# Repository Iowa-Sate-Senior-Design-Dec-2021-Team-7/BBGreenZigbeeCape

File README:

--Senior Design--
_________________________________________________________________________________________

Title: BeagleBone Green Gateway IoT Hub

Website: https://sddec21-07.sd.ece.iastate.edu

Project email: sddec21-07@iastate.edu

Trello board: https://trello.com/b/s8RNrqa7

Devs:
	-- Parker Larsen (pjlarsen)
	-- Taylor Weil (tcweil)
	-- Sterling Hulling (shulling)
	-- Sean Griffen (griffens)
_________________________________________________________________________________________

See CHANGELOG for official release updates/changes
_________________________________________________________________________________________

Scope:
	-- 
	
Stretch scope:
	-- 
_________________________________________________________________________________________

Requirements (in no particular order):
	-- 
	
Stretch Requirements (in no particular order):
	-- 
_________________________________________________________________________________________

Directory Roles:
	-- hardware: for pcb designs created and other hardware-specific resources
	-- firmware: for code being deployed on the BeagleBone Green Gateway, IoT cape, or other created daughter boards
	-- software: for code not being deployed on a hardware module. i.e. web-servers, apps, and other non-controller code
	-- docs: for project documents and classwork
_________________________________________________________________________________________

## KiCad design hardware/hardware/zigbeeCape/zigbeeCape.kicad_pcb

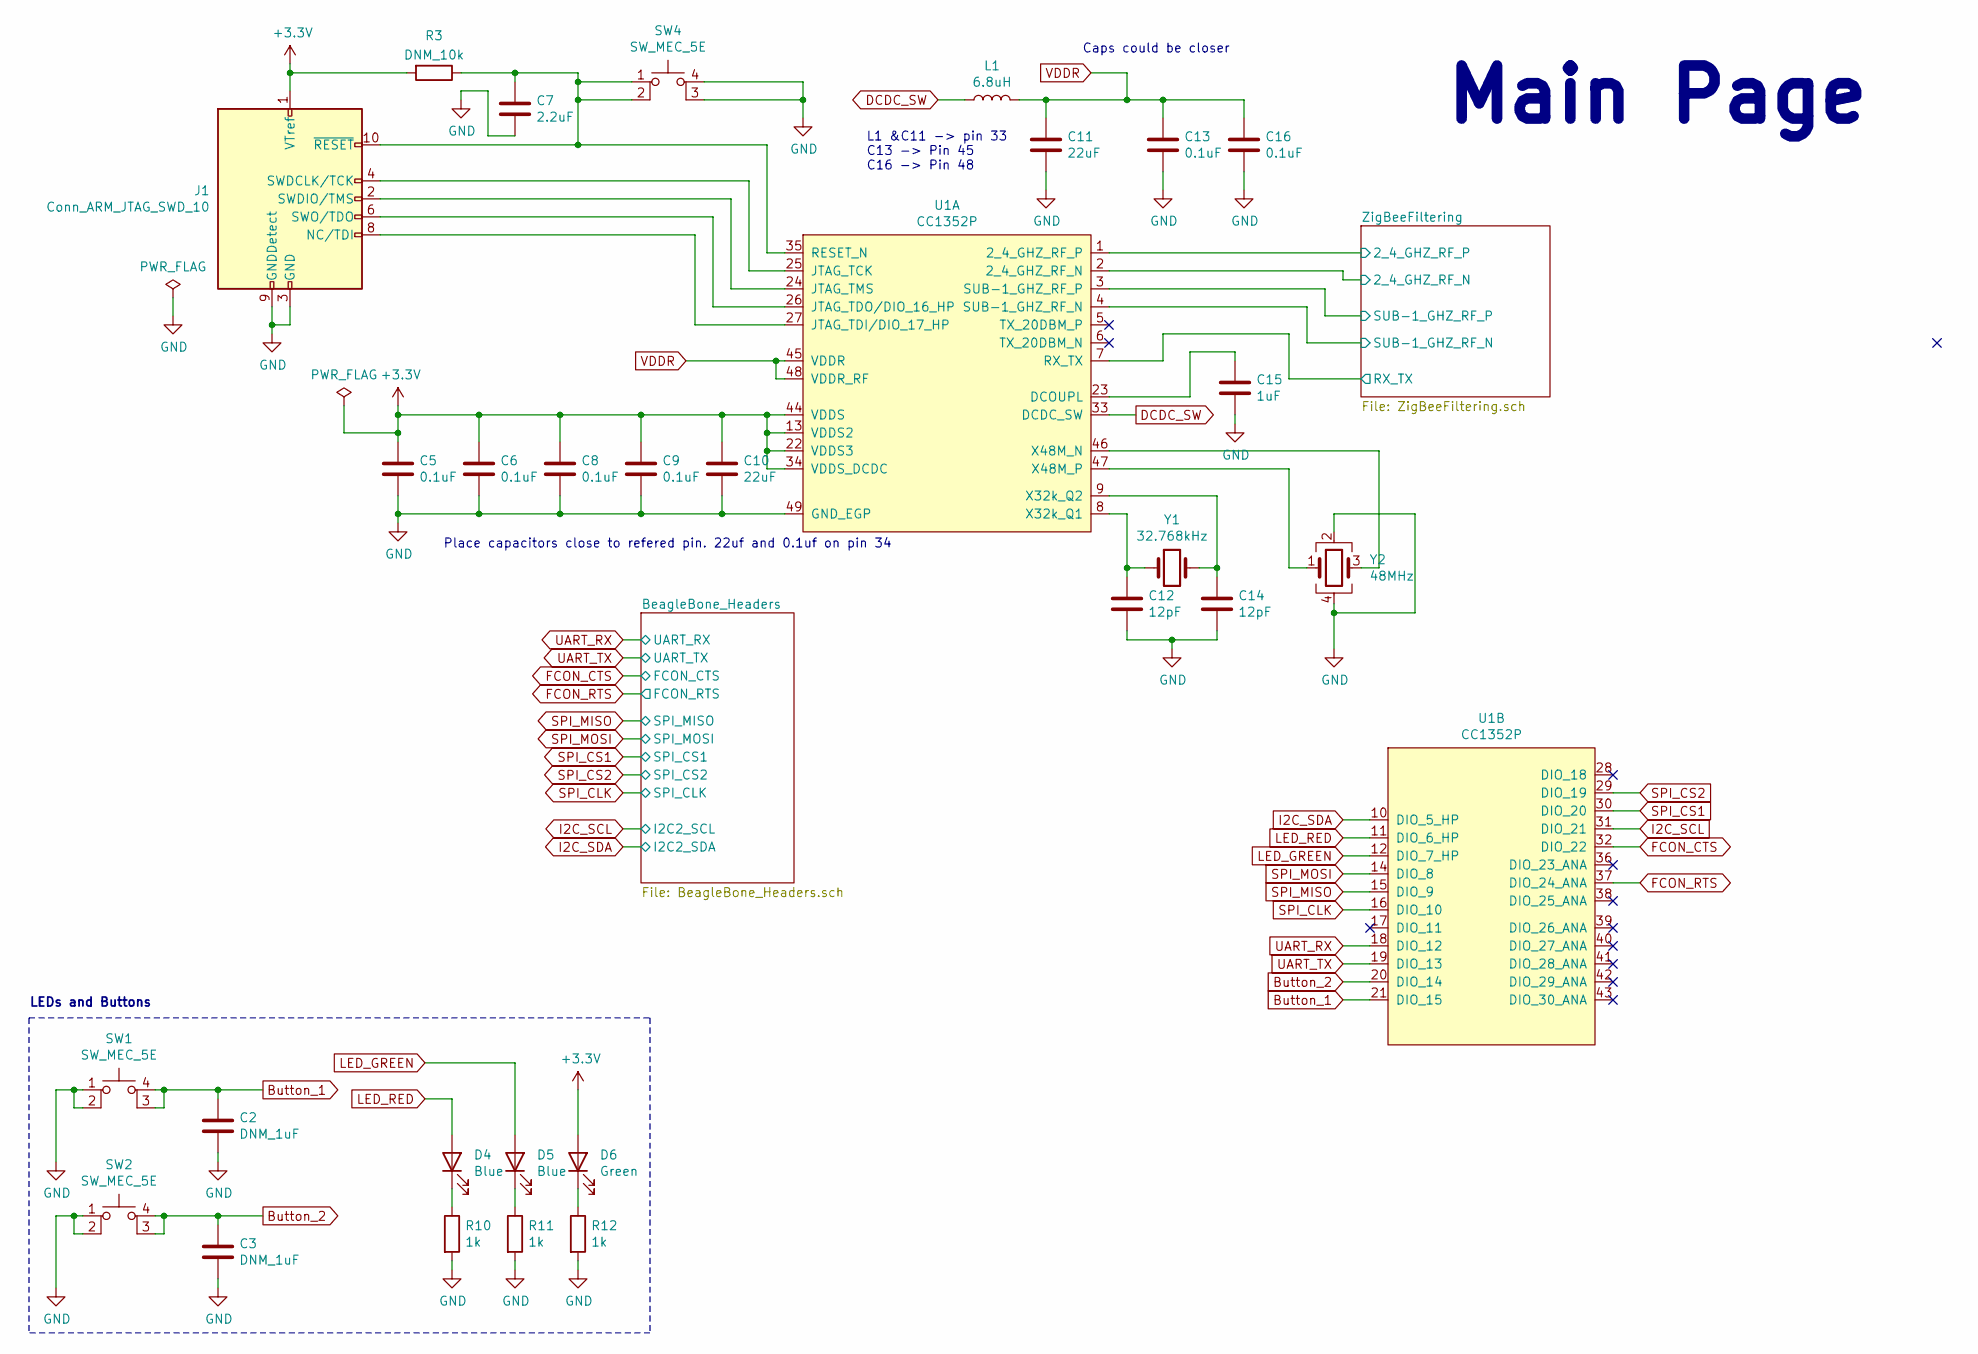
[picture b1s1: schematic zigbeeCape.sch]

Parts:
C2, C3: DNM_1uF; C_0603_1608Metric_Pad1.08x0.95mm_HandSolder; Digikey Part Number 1276-1184-1-ND
C5, C6, C8, C9, C13, C16: 0.1uF; C_0603_1608Metric_Pad1.08x0.95mm_HandSolder; Digikey Part Number 311-1777-1-ND
C7: 2.2uF; C_0603_1608Metric_Pad1.08x0.95mm_HandSolder; Digikey Part Number 1276-1085-1-ND
C10, C11: 22uF; C_0603_1608Metric_Pad1.08x0.95mm_HandSolder; Digikey Part Number 490-7611-1-ND
C12, C14: 12pF; C_0402_1005Metric_Pad0.74x0.62mm_HandSolder; Digikey Part Number 490-5924-1-ND
C15: 1uF; C_0603_1608Metric_Pad1.08x0.95mm_HandSolder; Digikey Part Number 1276-1184-1-ND
D4, D5: Blue; LED_0603_1608Metric_Pad1.05x0.95mm_HandSolder; Digikey Part Number 475-2815-1-ND
D6: Green; LED_0603_1608Metric_Pad1.05x0.95mm_HandSolder; Digikey Part Number 67-2320-1-ND
J1: Conn_ARM_JTAG_SWD_10; Digikey Part Number 1175-1621-ND
L1: 6.8uH; L_0805_2012Metric_Pad1.15x1.40mm_HandSolder; Digikey Part Number 445-17082-1-ND
R3: DNM_10k; R_0603_1608Metric_Pad0.98x0.95mm_HandSolder; Digikey Part Number 13-RT0603FRE1310KLCT-ND
R10, R11, R12: 1k; R_0603_1608Metric_Pad0.98x0.95mm_HandSolder; Digikey Part Number RMCF0603FT1K00CT-ND
SW1, SW2, SW4: SW_MEC_5E; SMD_PUSH_BUTTON; Digikey Part Number 679-2381-1-ND
U1: CC1352P; CC1352R
Y1: 32.768kHz; FC-135_Crystal_Unit; Digikey Part Number 2195-CC5V-T1A-32.768KHZ-7PF-20PPM-TA-QC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
Y2: 48MHz; SXT32418FD16-48MHZ_Crystal; Digikey Part Number 535-13996-1-ND

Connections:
+3V3: C5.1, C6.1, C8.1, C9.1, C10.1, D6.2 (A), J1.1 (VTref), R3.2, U1.13 (VDDS2), U1.22 (VDDS3), U1.34 (VDDS_DCDC), U1.44 (VDDS); also elsewhere on the board
/ZigBeeFiltering/2_4_GHZ_RF_N: U1.2 (2_4_GHZ_RF_N); also elsewhere on the board
/ZigBeeFiltering/2_4_GHZ_RF_P: U1.1 (2_4_GHZ_RF_P); also elsewhere on the board
/ZigBeeFiltering/RX_TX: U1.7 (RX_TX); also elsewhere on the board
/ZigBeeFiltering/SUB-1_GHZ_RF_N: U1.4 (SUB-1_GHZ_RF_N); also elsewhere on the board
/ZigBeeFiltering/SUB-1_GHZ_RF_P: U1.3 (SUB-1_GHZ_RF_P); also elsewhere on the board
Button_1: C2.1, SW1.3 (K), SW1.4 (A), U1.21 (DIO_15)
Button_2: C3.1, SW2.3 (K), SW2.4 (A), U1.20 (DIO_14)
DCDC_SW: L1.1, U1.33 (DCDC_SW)
FCON_CTS: U1.32 (DIO_22); also elsewhere on the board
FCON_RTS: U1.37 (DIO_24_ANA); also elsewhere on the board
GND: C2.2, C3.2, C5.2, C6.2, C7.2, C8.2, C9.2, C10.2, C11.2, C12.2, C13.2, C14.2, C15.2, C16.2, J1.3 (GND), J1.5 (GND), J1.9 (GNDDetect), R10.2, R11.2, R12.2, SW1.1, SW1.2, SW2.1, SW2.2, SW4.3 (K), SW4.4 (A), U1.49 (GND_EGP), Y2.2, Y2.4; also elsewhere on the board
I2C_SCL: U1.31 (DIO_21); also elsewhere on the board
I2C_SDA: U1.10 (DIO_5_HP); also elsewhere on the board
LED_GREEN: D5.2 (A), U1.12 (DIO_7_HP)
LED_RED: D4.2 (A), U1.11 (DIO_6_HP)
unnamed: C7.1, J1.10 (~RESET~), R3.1, SW4.1, SW4.2, U1.35 (RESET_N)
unnamed: C12.1, U1.8 (X32k_Q1), Y1.1
unnamed: C14.1, U1.9 (X32k_Q2), Y1.2
unnamed: C15.1, U1.23 (DCOUPL)
unnamed: D4.1 (K), R10.1
unnamed: D5.1 (K), R11.1
unnamed: D6.1 (K), R12.1
unnamed: J1.2 (SWDIO/TMS), U1.24 (JTAG_TMS)
unnamed: J1.4 (SWDCLK/TCK), U1.25 (JTAG_TCK)
unnamed: J1.6 (SWO/TDO), U1.26 (JTAG_TDO/DIO_16_HP)
unnamed: J1.8 (NC/TDI), U1.27 (JTAG_TDI/DIO_17_HP)
unnamed: U1.46 (X48M_N), Y2.3
unnamed: U1.47 (X48M_P), Y2.1
SPI_CLK: U1.16 (DIO_10); also elsewhere on the board
SPI_CS1: U1.30 (DIO_20); also elsewhere on the board
SPI_CS2: U1.29 (DIO_19); also elsewhere on the board
SPI_MISO: U1.15 (DIO_9); also elsewhere on the board
SPI_MOSI: U1.14 (DIO_8); also elsewhere on the board
UART_RX: U1.18 (DIO_12); also elsewhere on the board
UART_TX: U1.19 (DIO_13); also elsewhere on the board
VDDR: C11.1, C13.1, C16.1, L1.2, U1.45 (VDDR), U1.48 (VDDR_RF)

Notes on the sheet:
LEDs and Buttons
Place capacitors close to refered pin. 22uf and 0.1uf on pin 34
Main Page
Caps could be closer
L1 &C11 -> pin 33 C13 -> Pin 45 C16 -> Pin 48

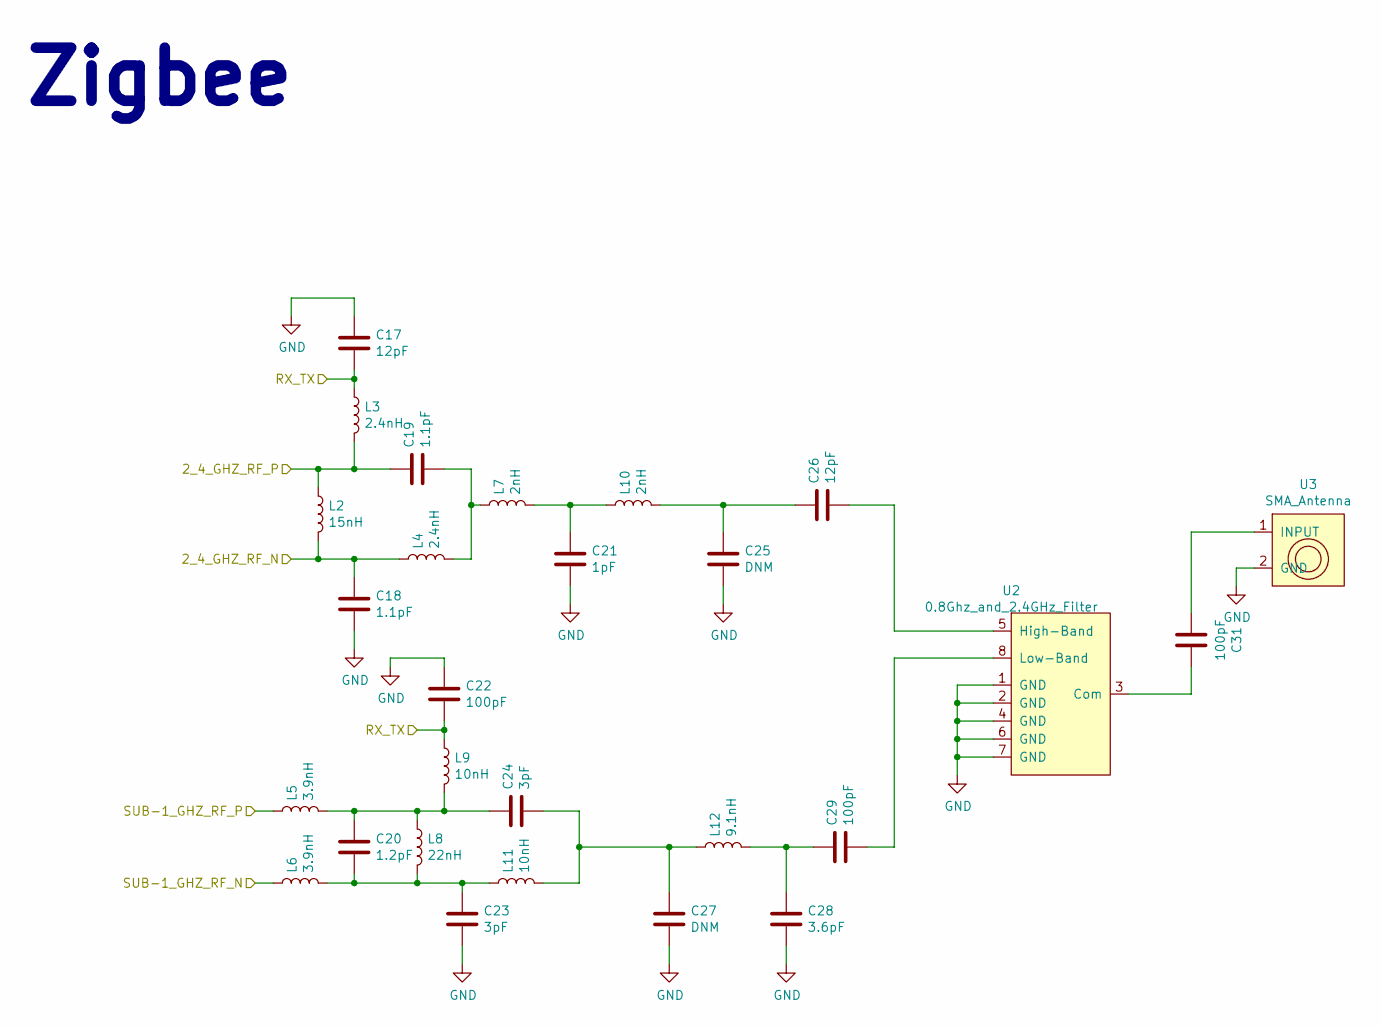
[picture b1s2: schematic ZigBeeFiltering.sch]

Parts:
C17, C26: 12pF; C_0402_1005Metric_Pad0.74x0.62mm_HandSolder; Digikey Part Number 490-5924-1-ND
C18, C19: 1.1pF; C_0402_1005Metric_Pad0.74x0.62mm_HandSolder; Digikey Part Number 490-8189-1-ND
C20: 1.2pF; C_0402_1005Metric_Pad0.74x0.62mm_HandSolder; Digikey Part Number 490-6209-1-ND
C21: 1pF; C_0402_1005Metric_Pad0.74x0.62mm_HandSolder; Digikey Part Number 478-3659-1-ND
C22, C29, C31: 100pF; C_0402_1005Metric_Pad0.74x0.62mm_HandSolder; Digikey Part Number 490-5922-1-ND
C23, C24: 3pF; C_0402_1005Metric_Pad0.74x0.62mm_HandSolder; Digikey Part Number 490-5872-1-ND
C25, C27: DNM; C_0402_1005Metric_Pad0.74x0.62mm_HandSolder; Digikey Part Number 490-5939-1-ND
C28: 3.6pF; C_0402_1005Metric_Pad0.74x0.62mm_HandSolder; Digikey Part Number 490-5939-1-ND
L2: 15nH; L_0402_1005Metric_Pad0.77x0.64mm_HandSolder; Digikey Part Number 490-2625-1-ND
L3, L4: 2.4nH; L_0402_1005Metric_Pad0.77x0.64mm_HandSolder; Digikey Part Number 490-8389-1-ND
L5, L6: 3.9nH; L_0402_1005Metric_Pad0.77x0.64mm_HandSolder; Digikey Part Number 490-2617-1-ND
L7, L10: 2nH; L_0402_1005Metric_Pad0.77x0.64mm_HandSolder; Digikey Part Number 490-6569-1-ND
L8: 22nH; L_0402_1005Metric_Pad0.77x0.64mm_HandSolder; Digikey Part Number 490-2627-1-ND
L9, L11: 10nH; L_0402_1005Metric_Pad0.77x0.64mm_HandSolder; Digikey Part Number 490-2623-1-ND
L12: 9.1nH; L_0402_1005Metric_Pad0.77x0.64mm_HandSolder; Digikey Part Number 490-8390-1-ND
U2: 0.8Ghz_and_2.4GHz_Filter; DPX252690DT-5032B1; Digikey Part Number 445-174204-1-ND
U3: SMA_Antenna; SMA_Amphenol_132134-16_Vertical; Digikey Part Number ACX1230-ND

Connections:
/ZigBeeFiltering/2_4_GHZ_RF_N: C18.1, L2.2, L4.1; also elsewhere on the board
/ZigBeeFiltering/2_4_GHZ_RF_P: C19.1, L2.1, L3.2; also elsewhere on the board
/ZigBeeFiltering/RX_TX: C17.2, C22.2, L3.1, L9.1; also elsewhere on the board
/ZigBeeFiltering/SUB-1_GHZ_RF_N: L6.1; also elsewhere on the board
/ZigBeeFiltering/SUB-1_GHZ_RF_P: L5.1; also elsewhere on the board
GND: C17.1, C18.2, C21.2, C22.1, C23.2, C25.2, C27.2, C28.2, U2.1 (GND), U2.2 (GND), U2.4 (GND), U2.6 (GND), U2.7 (GND), U3.2 (GND); also elsewhere on the board
unnamed: C19.2, L4.2, L7.1
unnamed: C20.1, C24.1, L5.2, L8.1, L9.2
unnamed: C20.2, C23.1, L6.2, L8.2, L11.1
unnamed: C21.1, L7.2, L10.1
unnamed: C24.2, C27.1, L11.2, L12.1
unnamed: C25.1, C26.1, L10.2
unnamed: C26.2, U2.5 (High-Band)
unnamed: C28.1, C29.1, L12.2
unnamed: C29.2, U2.8 (Low-Band)
unnamed: C31.1, U2.3 (Com)
unnamed: C31.2, U3.1 (INPUT)

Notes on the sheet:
Zigbee

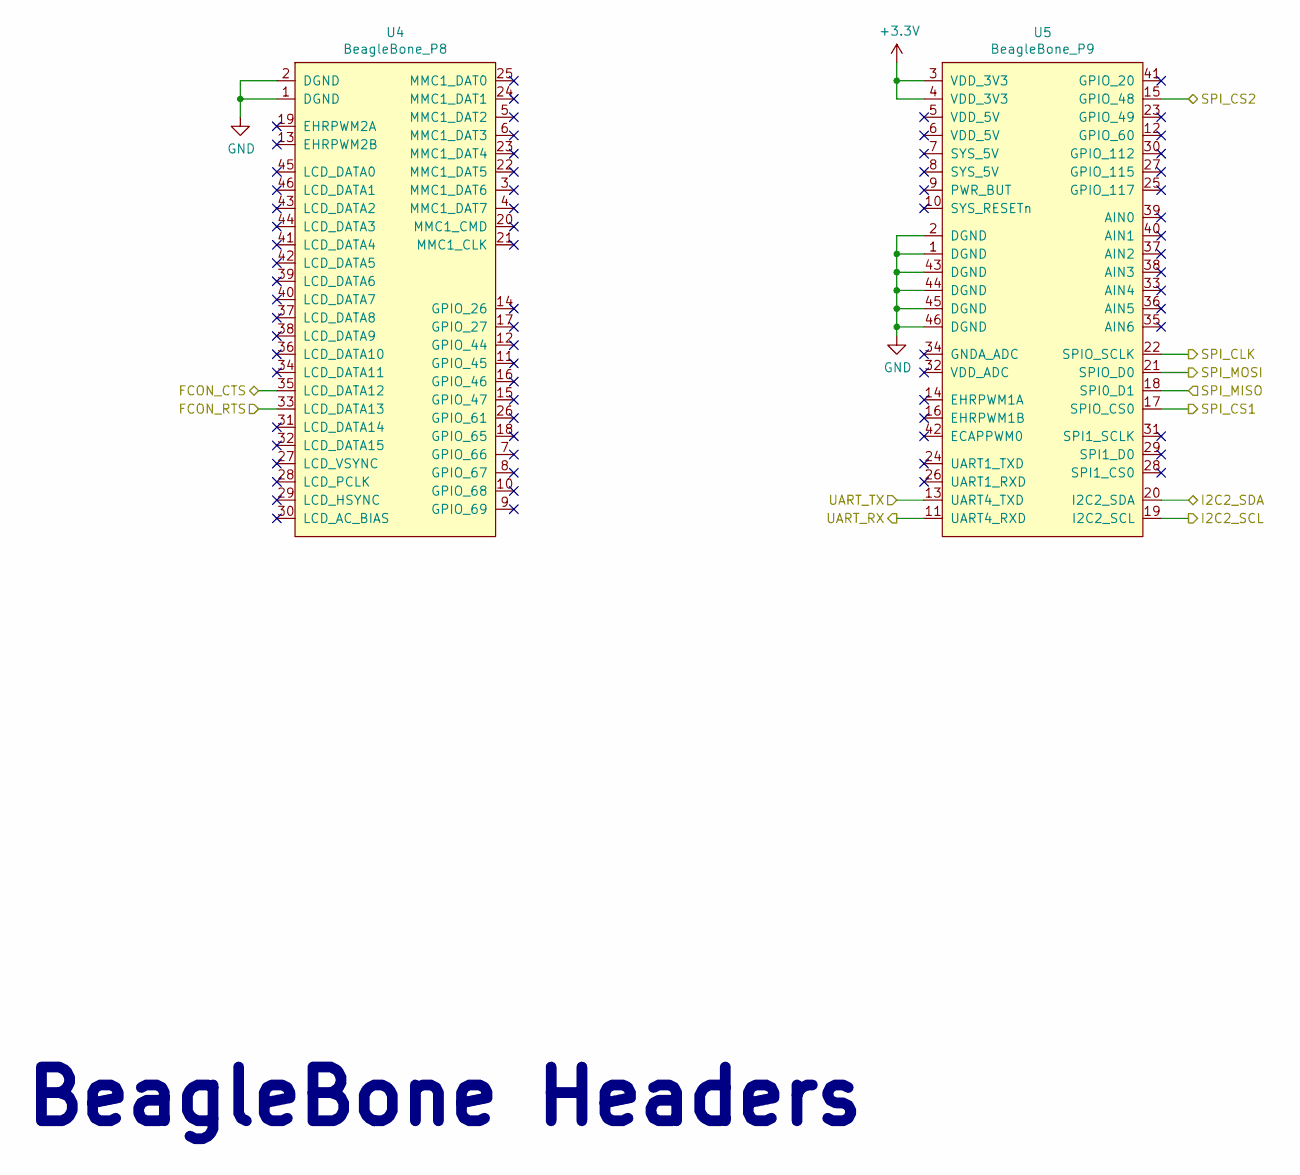
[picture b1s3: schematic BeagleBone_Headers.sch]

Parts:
U4: BeagleBone_P8; PinHeader_2x23_P2.54mm_Vertical; Digikey Part Number 1528-1365-ND
U5: BeagleBone_P9; PinHeader_2x23_P2.54mm_Vertical

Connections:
+3V3: U5.3 (VDD_3V3), U5.4 (VDD_3V3); also elsewhere on the board
FCON_CTS: U4.35 (LCD_DATA12); also elsewhere on the board
FCON_RTS: U4.33 (LCD_DATA13); also elsewhere on the board
GND: U4.1 (DGND), U4.2 (DGND), U5.1 (DGND), U5.2 (DGND), U5.43 (DGND), U5.44 (DGND), U5.45 (DGND), U5.46 (DGND); also elsewhere on the board
I2C_SCL: U5.19 (I2C2_SCL); also elsewhere on the board
I2C_SDA: U5.20 (I2C2_SDA); also elsewhere on the board
SPI_CLK: U5.22 (SPIO_SCLK); also elsewhere on the board
SPI_CS1: U5.17 (SPIO_CS0); also elsewhere on the board
SPI_CS2: U5.15 (GPIO_48); also elsewhere on the board
SPI_MISO: U5.18 (SPI0_D1); also elsewhere on the board
SPI_MOSI: U5.21 (SPIO_D0); also elsewhere on the board
UART_RX: U5.11 (UART4_RXD); also elsewhere on the board
UART_TX: U5.13 (UART4_TXD); also elsewhere on the board

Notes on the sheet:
BeagleBone Headers

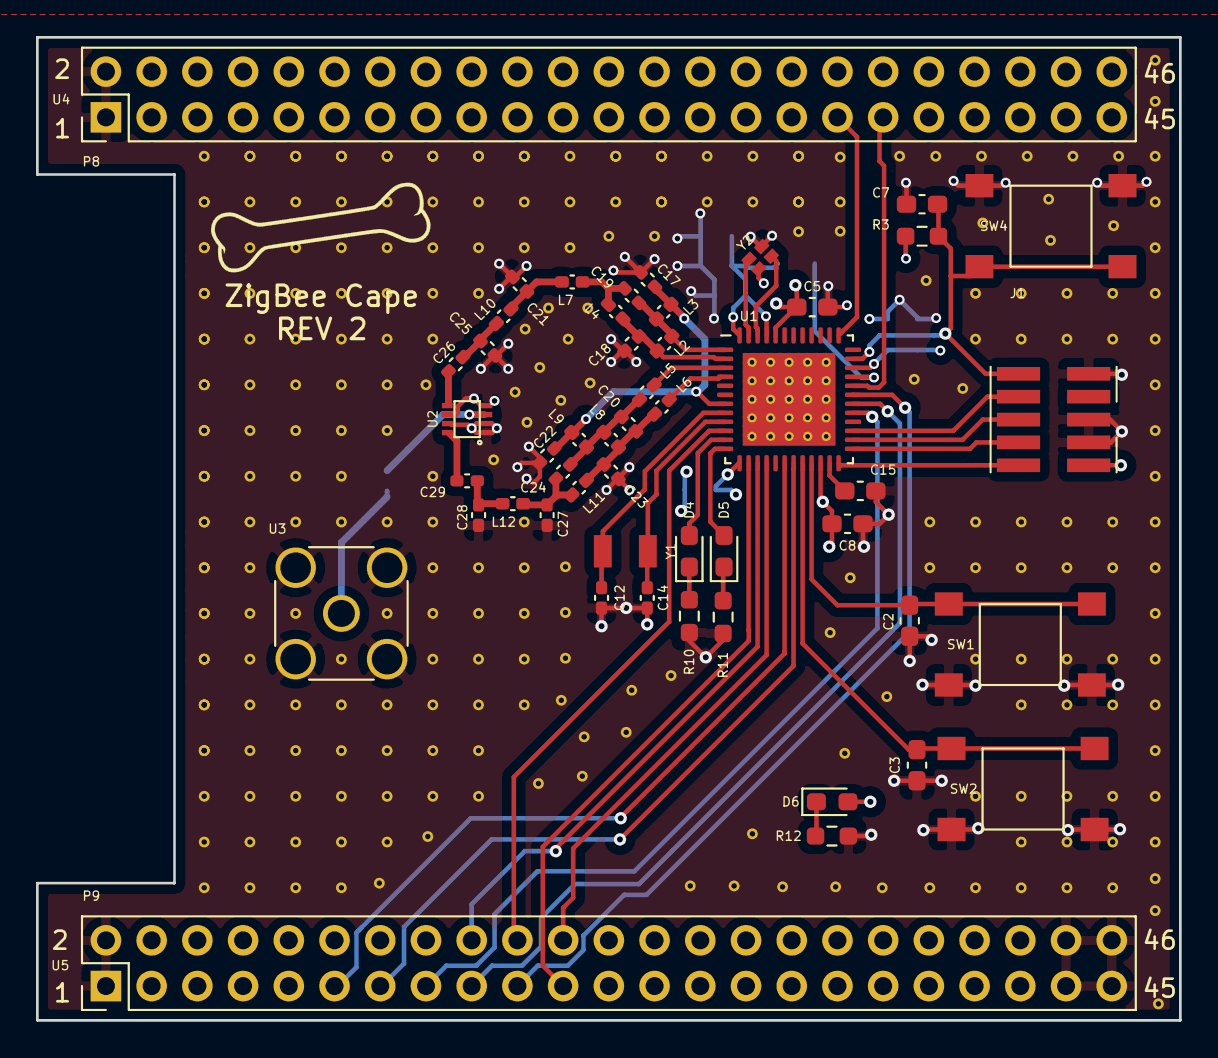
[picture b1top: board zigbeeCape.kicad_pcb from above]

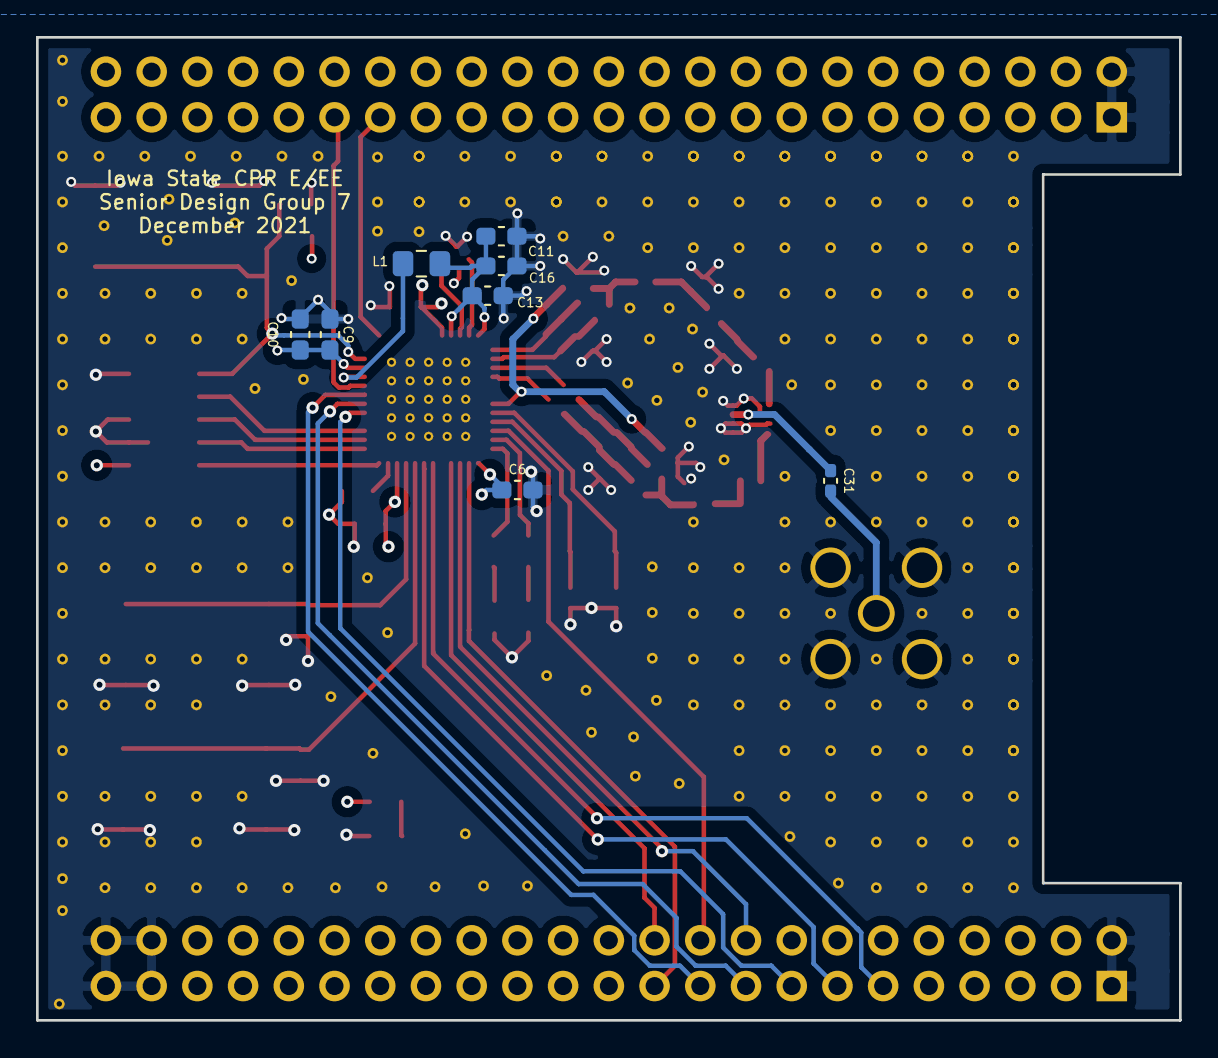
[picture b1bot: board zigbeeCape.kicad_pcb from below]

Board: 4 copper layers, 63.5 x 54.6 mm, 58 parts (8 on the bottom side), 48 nets.

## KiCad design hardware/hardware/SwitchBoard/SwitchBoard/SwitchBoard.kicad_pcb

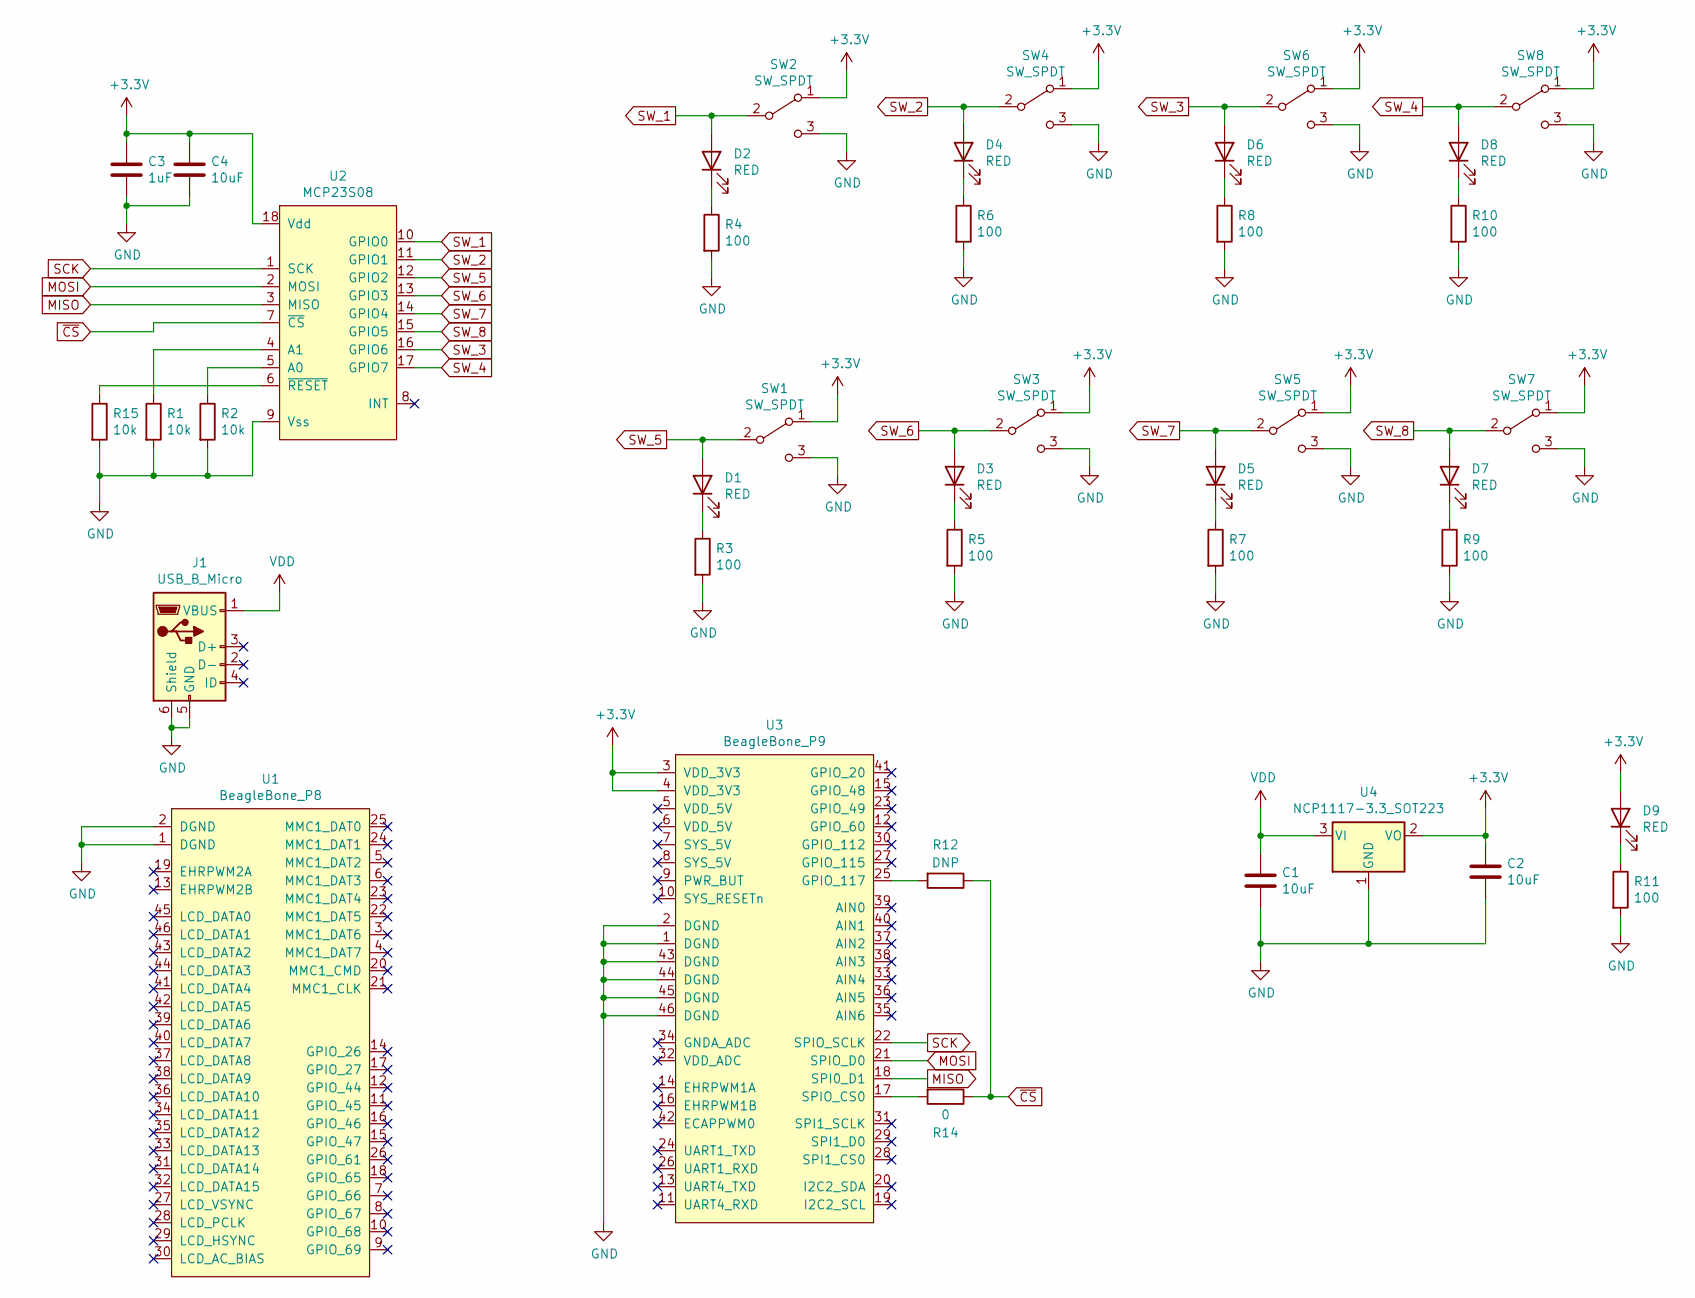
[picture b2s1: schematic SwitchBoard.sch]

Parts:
C1, C2, C4: 10uF; C_0603_1608Metric_Pad1.08x0.95mm_HandSolder; Digikey Part Number 1276-1038-1-ND
C3: 1uF; C_0603_1608Metric_Pad1.08x0.95mm_HandSolder; Digikey Part Number 311-1372-1-ND
D1, D2, D3, D4, D5, D6, D7, D8, D9: RED; D_0603_1608Metric_Pad1.05x0.95mm_HandSolder; Digikey Part Number 732-4978-1-ND
J1: USB_B_Micro; UJ2-MIBH2-4-SMT-TR; Digikey Part Number 102-4007-1-ND
R1, R2, R15: 10k; R_0603_1608Metric_Pad0.98x0.95mm_HandSolder; Digikey Part Number RMCF0603FT10K0CT-ND
R3, R4, R5, R6, R7, R8, R9, R10, R11: 100; R_0603_1608Metric_Pad0.98x0.95mm_HandSolder; Digikey Part Number 118-CR0603AFX-1000ELFCT-ND
R12: DNP; R_0603_1608Metric_Pad0.98x0.95mm_HandSolder
R14: 0; R_0603_1608Metric_Pad0.98x0.95mm_HandSolder; Digikey Part Number 541-0.0GCT-ND
SW1, SW2, SW3, SW4, SW5, SW6, SW7, SW8: SW_SPDT; DPDT; Digikey Part Number 401-2002-1-ND
U1: BeagleBone_P8; PinHeader_2x23_P2.54mm_Vertical; Digikey Part Number 1528-1365-ND
U2: MCP23S08; SOIC-18W_7.5x11.6mm_P1.27mm; Digikey Part Number MCP23S08-E/SO-ND
U3: BeagleBone_P9; PinHeader_2x23_P2.54mm_Vertical; Digikey Part Number NA
U4: NCP1117-3.3_SOT223; SOT-223-3_TabPin2; Digikey Part Number 488-NCP1117IST33T3GCT-ND

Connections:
+3V3: C2.1, C3.1, C4.1, D9.2 (A), SW1.1 (A), SW2.1 (A), SW3.1 (A), SW4.1 (A), SW5.1 (A), SW6.1 (A), SW7.1 (A), SW8.1 (A), U2.18 (Vdd), U3.3 (VDD_3V3), U3.4 (VDD_3V3), U4.2 (VO)
GND: C1.2, C2.2, C3.2, C4.2, J1.5 (GND), J1.6 (Shield), R1.2, R2.2, R3.2, R4.2, R5.2, R6.2, R7.2, R8.2, R9.2, R10.2, R11.2, R15.2, SW1.3 (C), SW2.3 (C), SW3.3 (C), SW4.3 (C), SW5.3 (C), SW6.3 (C), SW7.3 (C), SW8.3 (C), U1.1 (DGND), U1.2 (DGND), U2.9 (Vss), U3.1 (DGND), U3.2 (DGND), U3.43 (DGND), U3.44 (DGND), U3.45 (DGND), U3.46 (DGND), U4.1 (GND)
MISO: U2.3 (MISO), U3.18 (SPI0_D1)
MOSI: U2.2 (MOSI), U3.21 (SPIO_D0)
unnamed: D1.1 (K), R3.1
unnamed: D2.1 (K), R4.1
unnamed: D3.1 (K), R5.1
unnamed: D4.1 (K), R6.1
unnamed: D5.1 (K), R7.1
unnamed: D6.1 (K), R8.1
unnamed: D7.1 (K), R9.1
unnamed: D8.1 (K), R10.1
unnamed: D9.1 (K), R11.1
unnamed: R1.1, U2.4 (A1)
unnamed: R2.1, U2.5 (A0)
unnamed: R12.2, U3.25 (GPIO_117)
unnamed: R14.2, U3.17 (SPIO_CS0)
unnamed: R15.1, U2.6 (~RESET)
SCK: U2.1 (SCK), U3.22 (SPIO_SCLK)
SW_1: D2.2 (A), SW2.2 (B), U2.10 (GPIO0)
SW_2: D4.2 (A), SW4.2 (B), U2.11 (GPIO1)
SW_3: D6.2 (A), SW6.2 (B), U2.16 (GPIO6)
SW_4: D8.2 (A), SW8.2 (B), U2.17 (GPIO7)
SW_5: D1.2 (A), SW1.2 (B), U2.12 (GPIO2)
SW_6: D3.2 (A), SW3.2 (B), U2.13 (GPIO3)
SW_7: D5.2 (A), SW5.2 (B), U2.14 (GPIO4)
SW_8: D7.2 (A), SW7.2 (B), U2.15 (GPIO5)
VDD: C1.1, J1.1 (VBUS), U4.3 (VI)
~CS: R12.1, R14.1, U2.7 (~CS)

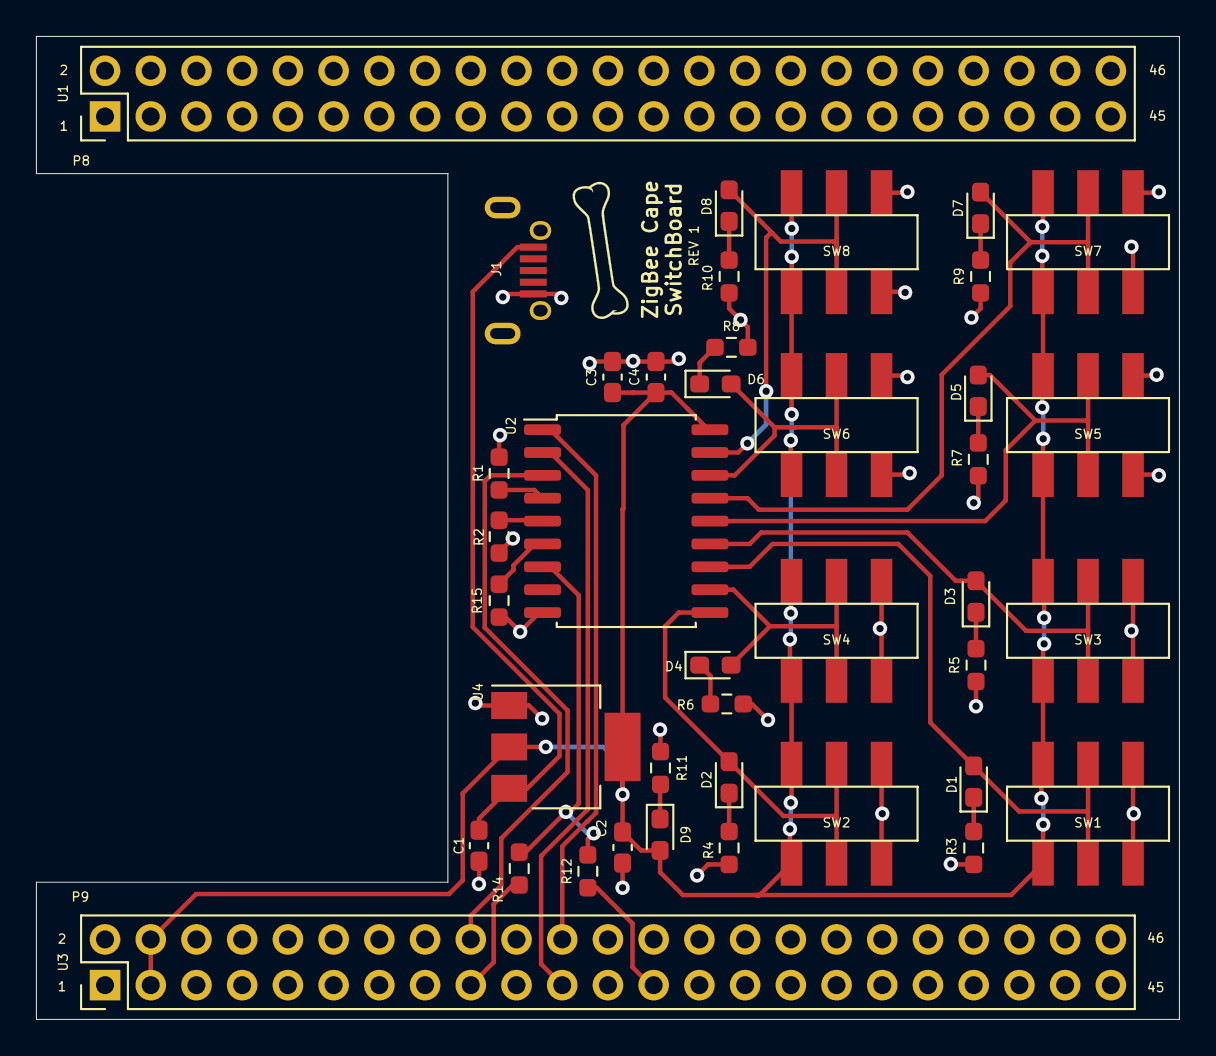
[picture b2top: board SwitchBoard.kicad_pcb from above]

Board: 2 copper layers, 63.5 x 54.6 mm, 40 parts (0 on the bottom side), 29 nets.

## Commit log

2021-02-05 Adding docs directory, and adding to README
2021-02-05 Updating CHANGELOG
2021-02-10 Adding Trello board link to README
2021-02-15 Adding first report to docs/
2021-02-22 Adding gitignore and updating CHANGELOG
2021-02-22 Adding directories for hw, fw, and sw projects
2021-03-01 Adding bi-monthly report 02
2021-03-15 Adding design doc and bimonthly report 3
2021-03-15 Updating CHANGELOG. Reserving use for branch merges from dev from now on, or for updates like official README changes. No need to put every little commit in the official CHANGELOT
2021-03-16 Adding directories for firmware. Updating README
2021-03-22 Adding Zigbee cape project, hardware folder structure
2021-03-22 Showing how to use git
2021-03-23 Setup KiCad libraries
2021-03-23 Adding software .gitignore
2021-03-23 Adding basic webserver for beaglebone to ping
2021-03-23 Seperating .gitignores into files based on what's located in the main directories. I.e., a gitignore for hardware, a gitignore for software, a general gitignore, etc...
2021-03-23 Adding basic post request to send a string to
2021-03-25 Adding test script to show interaction between Beaglebone and a webhost
2021-03-29 Adding base project for zigbee daughterboard demo
2021-03-29 Created and Added new block diagram
2021-03-29 Adding Symbol libraries
2021-03-29 Created symbol for CC1352R
2021-03-29 LIbrary updates
2021-04-01 Add new file
2021-04-01 Adding autoupdate script for the beaglebone that pulls the latest firmware files from the git repo
2021-04-05 Added schematic symbol P9(BeagleBone Header)
2021-04-05 Renamed P9->BeagleBone_P9, Added BeagleBone_P8
2021-04-05 Added LEDs and buttons
2021-04-05 Forgot a file
2021-04-06 Fixed LED names
2021-04-06 Adding design document v2
2021-04-06 Updating .gitignore to include dia autosave files
2021-04-06 removing dia autosave files
2021-04-06 updating design document .docx
2021-04-13 Adding bi-weekly report 5
2021-04-13 Added Most of Sub-1 Circuitry and most of Zigbee POwer Circuitry
2021-04-15 added footprint of CC1352R and PCB pin headers
2021-04-16 Checked Schematic is correct. Added PCB outline and verified Pin spacing.
2021-04-19 Finished Zigbee circuitry
2021-04-19 Updated CC1352 Naming
2021-04-19 Finished JTAG header
2021-04-19 More coms lines are complete.
2021-04-24 Checked Parkers work on the schematic. Added commentary to indicate capacitor use for VDDS
2021-04-26 Adding design document v3
2021-04-27 Added Functional Diagram
2021-04-27 Added/Changed a couple diagrams
2021-04-27 Added I2C pins, added signal wires to zigbee micro, fixed reset pin error
2021-04-28 Added beaglebone header heiarcy pins
2021-04-29 Assigned Pin types, cleaned stuff up, Fixed most errors from the DRC (questions on the last few)
2021-04-30 Added FL3 2.4ghz filter DPX252690DT-5032B1
2021-04-30 Fixed a few little things
2021-05-02 Added CC1352 and Sample BOM
2021-05-02 Made Corrections from Schematic Review
2021-05-02 Added Pin Usage Chart
2021-05-02 Fixing Git issue
2021-05-03 Started BOM
2021-05-07 Created footprint for DPX252690DT-5032B1 Diplexer filter
2021-05-12 Setting up libraries
2021-05-13 Added excell file to document deviations from CC1352R1 footprint size. Started assigning Footprints for Zigbee cape
2021-05-13 Added items to BOM. Added footprints to GIT. Finished Capacitor footprint association. Finished LED footprint association.
2021-05-14 Added all Capacitors to BOM
2021-05-21 Completed BOM except unlabled DNM parts, labled in red. Completed footprint association except onboard antenae
2021-06-10 Updated R1 on schematic, Updated R1 on BOM, add alt for button
2021-06-27 Changed push button, Started layout
2021-06-30 Layout Planning done, uC Done
2021-07-01 Buttons, most LEDs are done
2021-07-01 Setup DRC, completed coms lines
2021-07-01 Finished ZigBee circuit, Removed PCB antenna
2021-07-01 Small layout change
2021-07-07 Fixed a couple schematic symbols
2021-07-07 Changed min via size, rerouted lan/wifi, cleaned up traces
2021-07-07 Added Layout title and adjusted part refs
2021-07-09 Post layout review 1 changes
2021-07-09 Add ViaStitch-0.6 part, started stitching gnd planes
2021-08-02 Added more ground vias and silkscreen pin labels for the headers
2021-08-08 Added Schematic pdf
2021-08-08 Added Impedance Info and Calcuations
2021-08-09 Rerouted main ZigBee Lines
2021-08-09 Changed micro for soldering
2021-08-11 Almost done with traces
2021-08-23 Updated BOM, small changes to PCB and schematic
2021-08-24 Another BOM update
2021-08-25 Updated properties for faster BOM generation
2021-08-26 'sen', ~'son'
2021-09-02 Finished traces, a couple problems with the design rules
2021-09-02 added example ccs code
2021-09-16 Fixed some trace spacing things
2021-09-16 Finished up the stitching vias
2021-09-16 Fix silk screen, fixed via stitching net
2021-09-23 - Updating README format - Updating .gitignore with code composer studio stuff
2021-09-23 Fixed micro footprint, changed impedance to jlc, add thermal relief
2021-09-23 - Updating CHANGELOG
2021-09-24 Added gerber files
2021-09-27 Fixed micro, filter, push button footprints and fixed layout
2021-09-28 Finished layout, checking highspeed before turning it in
2021-09-29 Refreshed gerbers, ordered board, saved order files
2021-09-30 - Adding uart test code for cape and beaglebone - beaglebone UART1 sends a random character, cape echos character - Updating .gitignore for firmware - Re-organizing beaglebone test directories
2021-09-30 - Updating base .gitignore again
2021-09-30 add web app
2021-10-10 Added KiCad Project for Relay module. Relay Module schematic v1 ready.
2021-10-12 Started Switch Project, Finished Schematic
2021-10-12 Finished Switchboard schematic and BOM
2021-10-21 Finished schematic, BOM and started layout
2021-10-21 More progress on switchboard
2021-10-24 - Adding more in-depth uart test projects and the start of a uart json project
2021-10-24 added CC1352 projects
2021-10-27 Finished Layout with exception of power input
2021-10-28 moved projects to firmware
2021-10-28 removed files
2021-11-04 added cape project for sean to test
2021-11-07 More switchboard updates
2021-11-08 Switchboardrev1 Complete
2021-11-08 Cape_v2 schematic complete
2021-11-08 Fixing some footprint directories
2021-11-09 Almost done with layout
2021-11-09 Finished ZigBee Cape Rev 2
2021-11-09 Finished Capev2 and switchv1
2021-11-09 Finished and ordered boards
2021-11-11 Updated BOM header
2021-11-15 - Adding CapeFirmware_R project (cape firmware compiled for CC1352R launchpad) - Adding tirtos project dependency - And more
2021-11-15 - Updating ccs cache
2021-11-15 - untracking .jxbrowser* from git
2021-11-15 - Updating CapeProject to get uart communication from cape -> bb working
2021-11-18 trying to make sensor project
2021-11-18 sensor data
2021-11-28 - Firmware updates for the cape - Cleaning firmware directory some more :P
2021-12-01 - Cleaning firmware folders - Updating cape projects - Updating cape tests
2021-12-01 - Adding demo projects to software/
2021-12-01 - Cleaning firmware folder some more - Re-adding desired projects after clean
2021-12-02 changed react to TS and added nav
2021-12-03 Working table to display data
2021-12-04 - Updating webhost api endpoints
2021-12-04 - updating firmware .gitignore
2021-12-04 Added a nice chart with some settings and mock data
2021-12-04 - Updating webhost config for deployment context
2021-12-04 devices working on fetch
2021-12-06 updated server and added settings
2021-12-07 Updated string sent over zigbee and fixed project
2021-12-08 Sensor Tag Ready for Demo
2021-12-09 Upload New File
2021-12-09 Added Zigbee ZipFile, cleaned up some files
2021-12-09 Removing Zip
2021-12-09 Ready for Demo
2021-12-11 - Cleaning project files - Updating beaglebone scripts - Adding LICENSE - Updating cape firmware
2021-12-11 - Cleaning project files
2021-12-11 - Updating README for software scope and requirements
2021-12-11 - Updating webhost project - Moving project files to correct places - Cleaning more files
2021-12-11 - Cleaning more project files :)
2021-12-11 - Organizing docs directory
2021-12-11 - Updating README.md
2021-12-11 - Fixing typos in README.md
2021-12-13 Update README.md
    - Adding links to wiki for home, and getting started
2021-12-13 Update README.md
    - Re organizing sections
    - Updating links to external resources
